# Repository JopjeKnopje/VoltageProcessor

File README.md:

# VoltageProcessor

A eurorack module that outputs the **sum** and **difference** of two inputs, you can also add a constant DC offset to the summing output.

## Motivation
The Beatstep Pro's pitch output cannot go lower than **2V**, the VCO I'm using has a range of approximately **0-5V**, so I had a way to subtract the **2V** off of the pitch output. This module does just that, I intend to just use 1 CV input and a constant DC offset at **-2V** to achieve an output of **0V** with a **2V** input. <br>
You could also use it as a small 2 -> 1 mixer.

### Notes
This is my second KiCad project in a long time so the routing is not the best :) <br>
Measured the current consumption at **1mA @ +12V** and **7mA @ -12V**

## Bill of materials
|Reference|Value                        |Qty   |
|---------|-----------------------------|------|
|C1,C2,C3,C4|0.1uF                        |4     |
|C5,C6    |47uF                         |2     |
|J1,J2,J4,J5|PJ301M-12                    |4     |
|J3       |Eurorack power               |1     |
|R1,R2,R3,R4,R5,R6,R7,R8,R9,R10,R11,R12|100k                         |12    |
|R13,R14  |1k                           |2     |
|R15,R16  |10k                          |2     |
|RV1,RV2,RV3|100k                         |3     |
|U1       |TL074                        |1     |

[Interactive BOM](https://www.joppeboeve.nl/projects/voltage-processor/ibom.html)

[Falstad simulation](https://tinyurl.com/26u5qrzk)

## Schematic

## KiCad renders

### rev 0.2 -> 0.3 patches
- DC Offset potmeter range is now `+-10` instead of the rail-rail voltage.

### rev 0.1 -> 0.2 patches
- Flip eurorack power connector around y-axis, I currently use a flipped power cable as a workaround.
- Switch `U1B` and `U1B` terminals by adding jumper wire and cutting trace.
- J4 and J5 output should be on pin 3 instead of pin 2. fix by adding jumper wire.

## Todo
- [x] All of the `rev 0.1 patches`
- [ ] Fix jack hole should be 6mm instead of 5.3mm.
- [x] DC Offset potmeter compensate for opamp rail-rail offset which is around 1.3v
- [x] Add polarity symbol in C5 and C6.
- [x] Switch RV1 and RV2 twisting direction.
- [ ] Think about more ergonomic potmeter position.
- [x] Front panel
- [x] Produce and test rev 0.1

## Resources
[Summing Amplifier](https://www.electronics-tutorials.ws/opamp/opamp_4.html) 

[Differential Amplifier](https://www.electronics-tutorials.ws/opamp/opamp_5.html)

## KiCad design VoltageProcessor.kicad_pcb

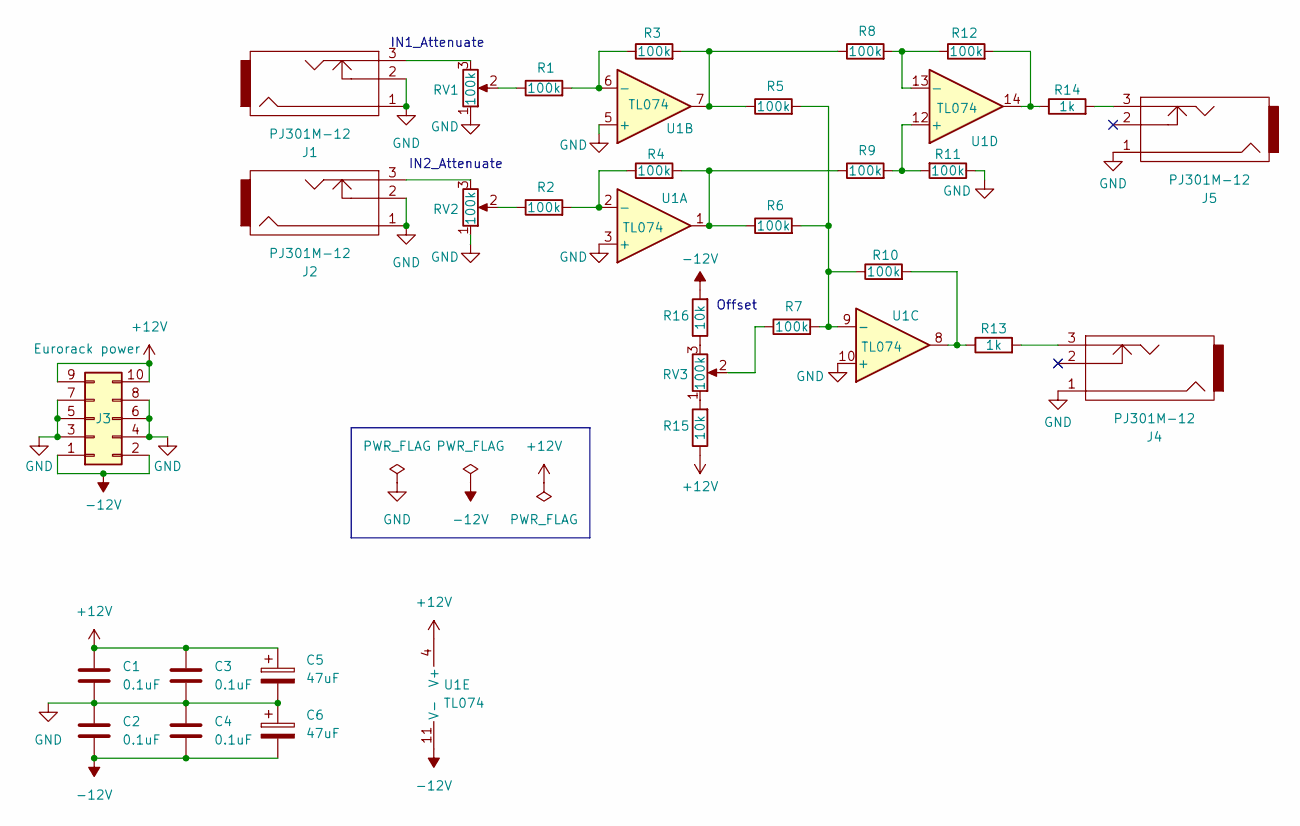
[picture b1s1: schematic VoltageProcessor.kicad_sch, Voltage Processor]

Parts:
C1, C2, C3, C4: 0.1uF; C_Disc_D5.0mm_W2.5mm_P2.50mm
C5, C6: 47uF; CP_Radial_D5.0mm_P2.00mm
J1, J2, J4, J5: PJ301M-12
J3: Eurorack power; IDC-Header_2x05_P2.54mm_Vertical
R1, R2, R3, R4, R5, R6, R7, R8, R9, R10, R11, R12: 100k; R_Axial_DIN0204_L3.6mm_D1.6mm_P7.62mm_Horizontal
R13, R14: 1k; R_Axial_DIN0204_L3.6mm_D1.6mm_P7.62mm_Horizontal
R15, R16: 10k; R_Axial_DIN0204_L3.6mm_D1.6mm_P7.62mm_Horizontal
RV1, RV2, RV3: 100k; trimmer_alps-rk09k1130ah1
U1: TL074; DIP-14_W7.62mm

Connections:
+12V: C1.1, C3.1, C5.1, J3.9, J3.10, R15.1, U1.4 (V+)
-12V: C2.2, C4.2, C6.2, J3.1, J3.2, R16.2, U1.11 (V-)
GND: C1.2, C2.1, C3.2, C4.1, C5.2, C6.1, J1.1, J1.2, J2.1, J2.2, J3.3, J3.4, J3.5, J3.6, J3.7, J3.8, J4.1, J5.1, R11.1, RV1.1, RV2.1, U1.3 (+), U1.5 (+), U1.10 (+)
unnamed: J1.3, RV1.3
unnamed: J2.3, RV2.3
unnamed: J4.3, R13.2
unnamed: J5.3, R14.2
unnamed: R1.1, RV1.2
unnamed: R2.1, RV2.2
unnamed: R3.2, R5.1, R8.1, U1.7
unnamed: R4.2, R6.1, R9.1, U1.1
unnamed: R7.1, RV3.2
unnamed: R10.2, R13.1, U1.8
unnamed: R12.2, R14.1, U1.14
unnamed: R15.2, RV3.1
unnamed: R16.1, RV3.3
unnamed: R2.2, R4.1, U1.2 (-)
unnamed: R1.2, R3.1, U1.6 (-)
unnamed: R5.2, R6.2, R7.2, R10.1, U1.9 (-)
unnamed: R9.2, R11.2, U1.12 (+)
unnamed: R8.2, R12.1, U1.13 (-)

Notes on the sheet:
IN1_Attenuate
Offset
IN2_Attenuate

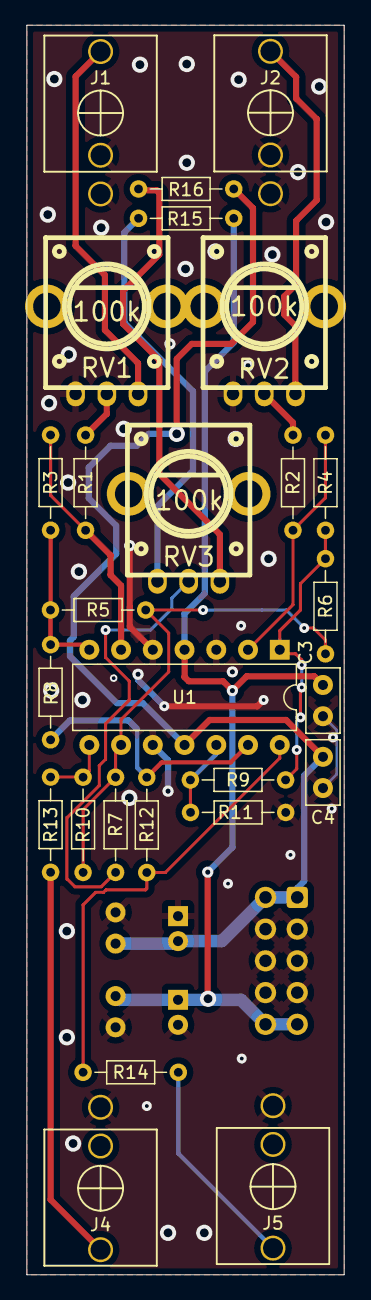
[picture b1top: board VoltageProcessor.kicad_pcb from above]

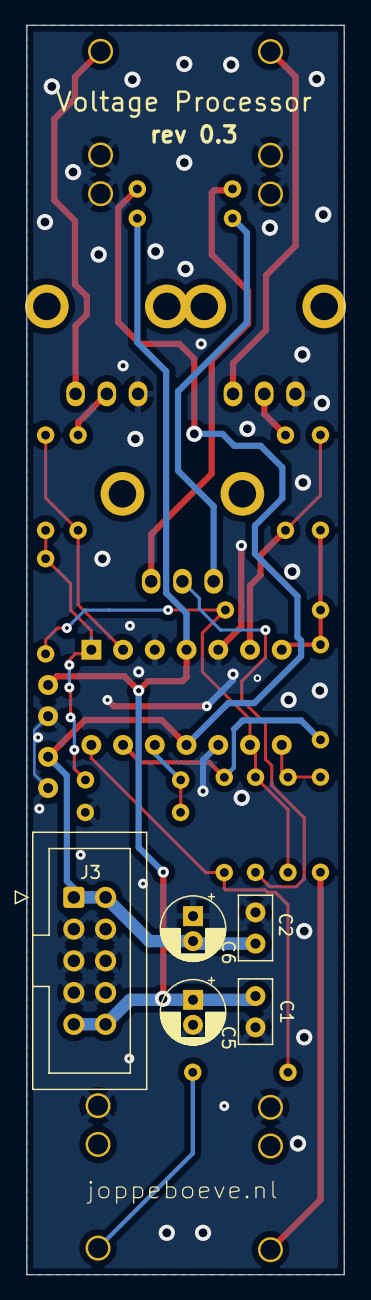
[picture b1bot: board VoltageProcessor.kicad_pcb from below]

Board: 2 copper layers, 25.4 x 100.0 mm, 31 parts (5 on the bottom side), 21 nets.

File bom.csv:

"Reference","Value","Qty"
"C1,C2,C3,C4","0.1uF","4"
"C5,C6","47uF","2"
"J1,J2,J4,J5","PJ301M-12","4"
"J3","Eurorack power","1"
"R1,R2,R3,R4,R5,R6,R7,R8,R9,R10,R11,R12","100k","12"
"R13,R14","1k","2"
"R15,R16","10k","2"
"RV1,RV2,RV3","100k","3"
"U1","TL074","1"

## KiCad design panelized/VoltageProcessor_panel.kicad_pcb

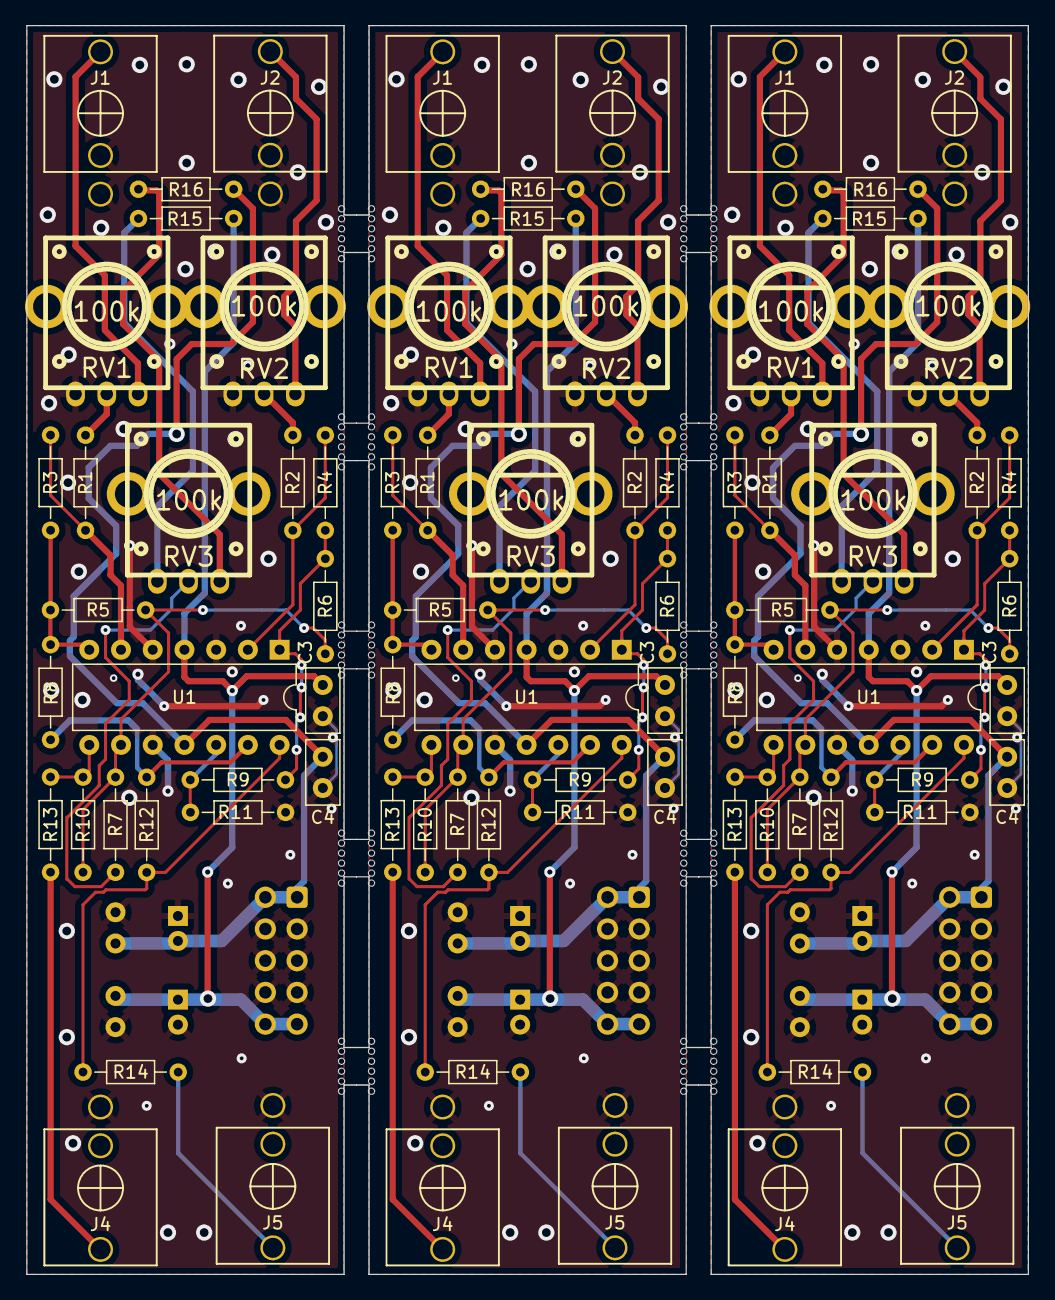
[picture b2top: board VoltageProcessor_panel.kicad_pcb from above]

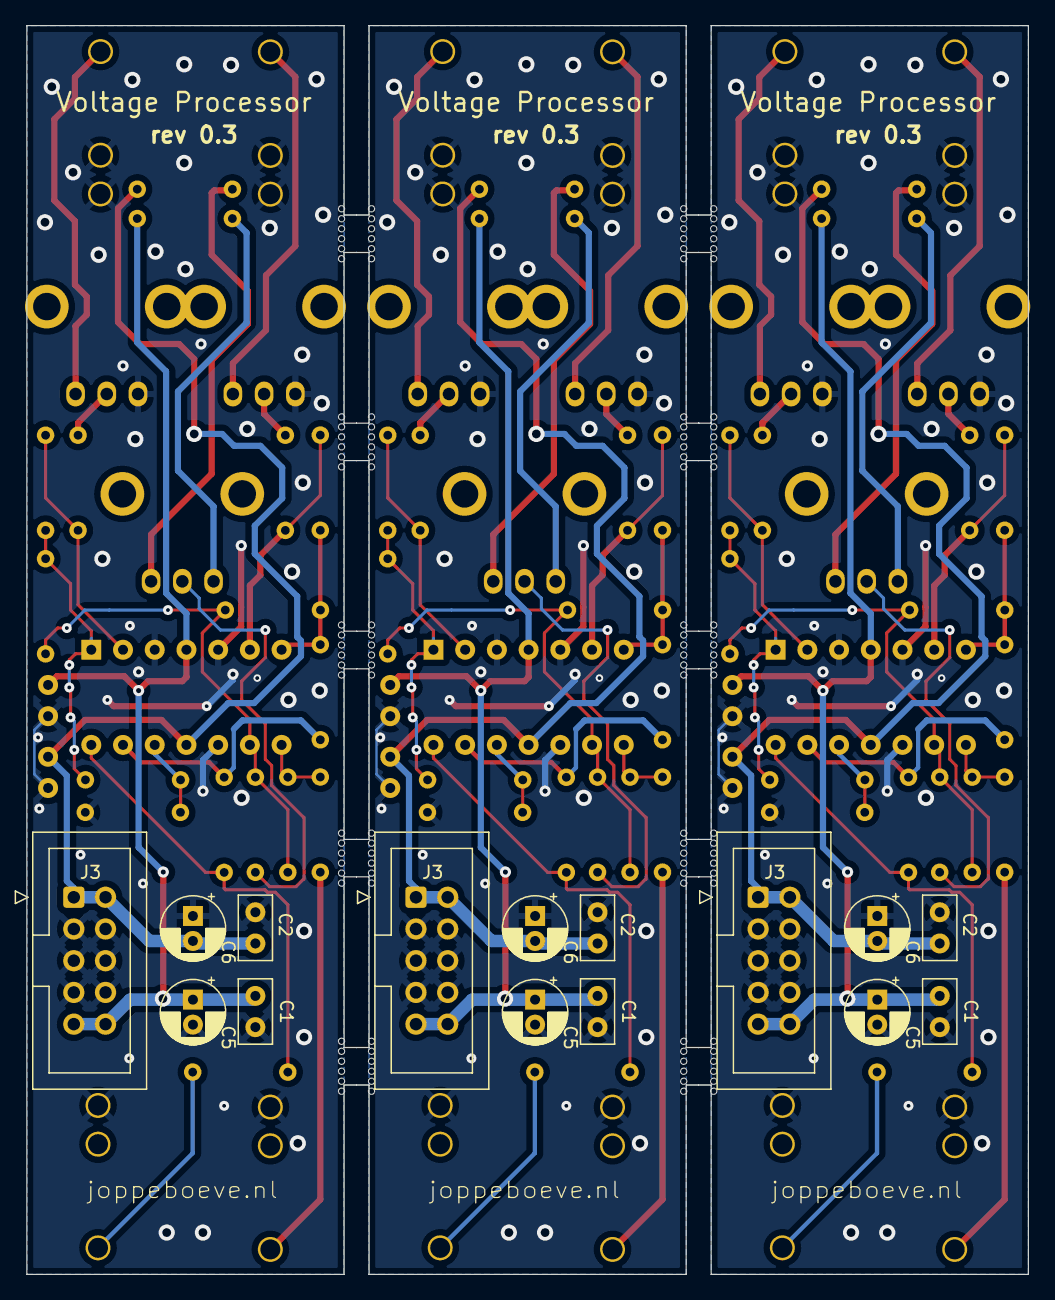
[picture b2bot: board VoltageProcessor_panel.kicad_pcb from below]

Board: 2 copper layers, 80.2 x 100.0 mm, 213 parts (15 on the bottom side), 63 nets.

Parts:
C1, C1#2, C1#3, C2, C2#2, C2#3, C3, C3#2, C3#3, C4, C4#2, C4#3: 0.1uF; C_Disc_D5.0mm_W2.5mm_P2.50mm
C5, C5#2, C5#3, C6, C6#2, C6#3: 47uF; CP_Radial_D5.0mm_P2.00mm
J1, J1#2, J1#3, J2, J2#2, J2#3, J4, J4#2, J4#3, J5, J5#2, J5#3: PJ301M-12
J3, J3#2, J3#3: Eurorack power; IDC-Header_2x05_P2.54mm_Vertical
KiKit_MB_1_1, KiKit_MB_1_2, KiKit_MB_1_3, KiKit_MB_1_4, KiKit_MB_1_5, KiKit_MB_1_6, KiKit_MB_2_1, KiKit_MB_2_2, KiKit_MB_2_3, KiKit_MB_2_4, KiKit_MB_2_5, KiKit_MB_2_6, KiKit_MB_3_1, KiKit_MB_3_2, KiKit_MB_3_3, KiKit_MB_3_4, KiKit_MB_3_5, KiKit_MB_3_6, KiKit_MB_4_1, KiKit_MB_4_2, KiKit_MB_4_3, KiKit_MB_4_4, KiKit_MB_4_5, KiKit_MB_4_6, KiKit_MB_5_1, KiKit_MB_5_2, KiKit_MB_5_3, KiKit_MB_5_4, KiKit_MB_5_5, KiKit_MB_5_6, KiKit_MB_6_1, KiKit_MB_6_2, KiKit_MB_6_3, KiKit_MB_6_4, KiKit_MB_6_5, KiKit_MB_6_6, KiKit_MB_7_1, KiKit_MB_7_2, KiKit_MB_7_3, KiKit_MB_7_4, KiKit_MB_7_5, KiKit_MB_7_6, KiKit_MB_8_1, KiKit_MB_8_2, KiKit_MB_8_3, KiKit_MB_8_4, KiKit_MB_8_5, KiKit_MB_8_6, KiKit_MB_9_1, KiKit_MB_9_2, KiKit_MB_9_3, KiKit_MB_9_4, KiKit_MB_9_5, KiKit_MB_9_6, KiKit_MB_10_1, KiKit_MB_10_2, KiKit_MB_10_3, KiKit_MB_10_4, KiKit_MB_10_5, KiKit_MB_10_6, KiKit_MB_11_1, KiKit_MB_11_2, KiKit_MB_11_3, KiKit_MB_11_4, KiKit_MB_11_5, KiKit_MB_11_6, KiKit_MB_12_1, KiKit_MB_12_2, KiKit_MB_12_3, KiKit_MB_12_4, KiKit_MB_12_5, KiKit_MB_12_6, KiKit_MB_13_1, KiKit_MB_13_2, KiKit_MB_13_3, KiKit_MB_13_4, KiKit_MB_13_5, KiKit_MB_13_6, KiKit_MB_14_1, KiKit_MB_14_2, KiKit_MB_14_3, KiKit_MB_14_4, KiKit_MB_14_5, KiKit_MB_14_6, KiKit_MB_15_1, KiKit_MB_15_2, KiKit_MB_15_3, KiKit_MB_15_4, KiKit_MB_15_5, KiKit_MB_15_6, KiKit_MB_16_1, KiKit_MB_16_2, KiKit_MB_16_3, KiKit_MB_16_4, KiKit_MB_16_5, KiKit_MB_16_6, KiKit_MB_17_1, KiKit_MB_17_2, KiKit_MB_17_3, KiKit_MB_17_4, KiKit_MB_17_5, KiKit_MB_17_6, KiKit_MB_18_1, KiKit_MB_18_2, KiKit_MB_18_3, KiKit_MB_18_4, KiKit_MB_18_5, KiKit_MB_18_6, KiKit_MB_19_1, KiKit_MB_19_2, KiKit_MB_19_3, KiKit_MB_19_4, KiKit_MB_19_5, KiKit_MB_19_6, KiKit_MB_20_1, KiKit_MB_20_2, KiKit_MB_20_3, KiKit_MB_20_4, KiKit_MB_20_5, KiKit_MB_20_6: NPTH
R1, R1#2, R1#3, R2, R2#2, R2#3, R3, R3#2, R3#3, R4, R4#2, R4#3, R5, R5#2, R5#3, R6, R6#2, R6#3, R7, R7#2, R7#3, R8, R8#2, R8#3, R9, R9#2, R9#3, R10, R10#2, R10#3, R11, R11#2, R11#3, R12, R12#2, R12#3: 100k; R_Axial_DIN0204_L3.6mm_D1.6mm_P7.62mm_Horizontal
R13, R13#2, R13#3, R14, R14#2, R14#3: 1k; R_Axial_DIN0204_L3.6mm_D1.6mm_P7.62mm_Horizontal
R15, R15#2, R15#3, R16, R16#2, R16#3: 10k; R_Axial_DIN0204_L3.6mm_D1.6mm_P7.62mm_Horizontal
RV1, RV1#2, RV1#3, RV2, RV2#2, RV2#3, RV3, RV3#2, RV3#3: 100k; trimmer_alps-rk09k1130ah1
U1, U1#2, U1#3: TL074; DIP-14_W7.62mm

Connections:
Board_0-+12V: C1#2.1, C3#2.1, C5.1, J3#3.9, J3#3.10, R15#2.1, U1#2.4 (V+)
Board_0--12V: C2#3.2, C4#2.2, C6#2.2, J3#3.1, J3#3.2, R16#2.2, U1#2.11 (V-)
Board_0-GND: C1#2.2, C2#3.1, C3#2.2, C4#2.1, C5.2, C6#2.1, J1#2.1, J1#2.2, J2.1, J2.2, J3#3.3, J3#3.4, J3#3.5, J3#3.6, J3#3.7, J3#3.8, J4#3.1, J5#2.1, R11#2.1, RV1.1, RV2#2.1, U1#2.3 (+), U1#2.5 (+), U1#2.10 (+)
Board_0-Net-(J1-Pad3): J1#2.3, RV1.3
Board_0-Net-(J2-Pad3): J2.3, RV2#2.3
Board_0-Net-(J4-Pad3): J4#3.3, R13#2.2
Board_0-Net-(J5-Pad3): J5#2.3, R14#2.2
Board_0-Net-(R1-Pad1): R1.1, RV1.2
Board_0-Net-(R2-Pad1): R2#2.1, RV2#2.2
Board_0-Net-(R3-Pad2): R3#3.2, R5#2.1, R8#2.1, U1#2.7
Board_0-Net-(R4-Pad2): R4#2.2, R6#3.1, R9.1, U1#2.1
Board_0-Net-(R7-Pad1): R7#3.1, RV3.2
Board_0-Net-(R10-Pad2): R10#3.2, R13#2.1, U1#2.8
Board_0-Net-(R12-Pad2): R12.2, R14#2.1, U1#2.14
Board_0-Net-(R15-Pad2): R15#2.2, RV3.1
Board_0-Net-(R16-Pad1): R16#2.1, RV3.3
Board_0-Net-(U1A--): R2#2.2, R4#2.1, U1#2.2 (-)
Board_0-Net-(U1B--): R1.2, R3#3.1, U1#2.6 (-)
Board_0-Net-(U1C--): R5#2.2, R6#3.2, R7#3.2, R10#3.1, U1#2.9 (-)
Board_0-Net-(U1D-+): R9.2, R11#2.2, U1#2.12 (+)
Board_0-Net-(U1D--): R8#2.2, R12.1, U1#2.13 (-)
Board_1-+12V: C1.1, C3.1, C5#2.1, J3.9, J3.10, R15.1, U1.4 (V+)
Board_1--12V: C2#2.2, C4.2, C6.2, J3.1, J3.2, R16#3.2, U1.11 (V-)
Board_1-GND: C1.2, C2#2.1, C3.2, C4.1, C5#2.2, C6.1, J1#3.1, J1#3.2, J2#3.1, J2#3.2, J3.3, J3.4, J3.5, J3.6, J3.7, J3.8, J4.1, J5#3.1, R11.1, RV1#3.1, RV2#3.1, U1.3 (+), U1.5 (+), U1.10 (+)
Board_1-Net-(J1-Pad3): J1#3.3, RV1#3.3
Board_1-Net-(J2-Pad3): J2#3.3, RV2#3.3
Board_1-Net-(J4-Pad3): J4.3, R13#3.2
Board_1-Net-(J5-Pad3): J5#3.3, R14.2
Board_1-Net-(R1-Pad1): R1#3.1, RV1#3.2
Board_1-Net-(R2-Pad1): R2#3.1, RV2#3.2
Board_1-Net-(R3-Pad2): R3#2.2, R5.1, R8.1, U1.7
Board_1-Net-(R4-Pad2): R4#3.2, R6#2.1, R9#2.1, U1.1
Board_1-Net-(R7-Pad1): R7#2.1, RV3#3.2
Board_1-Net-(R10-Pad2): R10.2, R13#3.1, U1.8
Board_1-Net-(R12-Pad2): R12#3.2, R14.1, U1.14
Board_1-Net-(R15-Pad2): R15.2, RV3#3.1
Board_1-Net-(R16-Pad1): R16#3.1, RV3#3.3
Board_1-Net-(U1A--): R2#3.2, R4#3.1, U1.2 (-)
Board_1-Net-(U1B--): R1#3.2, R3#2.1, U1.6 (-)
Board_1-Net-(U1C--): R5.2, R6#2.2, R7#2.2, R10.1, U1.9 (-)
Board_1-Net-(U1D-+): R9#2.2, R11.2, U1.12 (+)
Board_1-Net-(U1D--): R8.2, R12#3.1, U1.13 (-)
Board_2-+12V: C1#3.1, C3#3.1, C5#3.1, J3#2.9, J3#2.10, R15#3.1, U1#3.4 (V+)
Board_2--12V: C2.2, C4#3.2, C6#3.2, J3#2.1, J3#2.2, R16.2, U1#3.11 (V-)
Board_2-GND: C1#3.2, C2.1, C3#3.2, C4#3.1, C5#3.2, C6#3.1, J1.1, J1.2, J2#2.1, J2#2.2, J3#2.3, J3#2.4, J3#2.5, J3#2.6, J3#2.7, J3#2.8, J4#2.1, J5.1, R11#3.1, RV1#2.1, RV2.1, U1#3.3 (+), U1#3.5 (+), U1#3.10 (+)
Board_2-Net-(J1-Pad3): J1.3, RV1#2.3
Board_2-Net-(J2-Pad3): J2#2.3, RV2.3
Board_2-Net-(J4-Pad3): J4#2.3, R13.2
Board_2-Net-(J5-Pad3): J5.3, R14#3.2
Board_2-Net-(R1-Pad1): R1#2.1, RV1#2.2
Board_2-Net-(R2-Pad1): R2.1, RV2.2
Board_2-Net-(R3-Pad2): R3.2, R5#3.1, R8#3.1, U1#3.7
Board_2-Net-(R4-Pad2): R4.2, R6.1, R9#3.1, U1#3.1
Board_2-Net-(R7-Pad1): R7.1, RV3#2.2
Board_2-Net-(R10-Pad2): R10#2.2, R13.1, U1#3.8
Board_2-Net-(R12-Pad2): R12#2.2, R14#3.1, U1#3.14
Board_2-Net-(R15-Pad2): R15#3.2, RV3#2.1
Board_2-Net-(R16-Pad1): R16.1, RV3#2.3
Board_2-Net-(U1A--): R2.2, R4.1, U1#3.2 (-)
Board_2-Net-(U1B--): R1#2.2, R3.1, U1#3.6 (-)
Board_2-Net-(U1C--): R5#3.2, R6.2, R7.2, R10#2.1, U1#3.9 (-)
Board_2-Net-(U1D-+): R9#3.2, R11#3.2, U1#3.12 (+)
Board_2-Net-(U1D--): R8#3.2, R12#2.1, U1#3.13 (-)

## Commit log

2024-07-26 IO Placement
2024-07-26 Pre route
2024-07-26 Done with routing but DRC issues
2024-07-26 Fix most DRC errors
2024-07-28 Add silkscreen text, and last DRC issues
2024-07-28 Add 3D models
2024-07-28 Add image to readme
2024-07-28 Connected input CV jack's switch to GND instead of NC Add schematic picture
2024-07-28 remove `)` from README.md
2024-07-28 Add gerbers Add 3D model back in Add kikit makefile to generate panel
2024-07-28 Add panelized files
2024-07-28 Add FrontPanel
2024-07-28 Add frontpanel gerbers
2024-07-28 Change Makefile Add FrontPanel_panels
2024-07-28 Actually add front_panel gebers
2024-08-02 Found some bugs while assembling the board
2024-08-02 Add issues
2024-08-05 Swapped `U1B` inputs to match that of `U1A`, so that it does work
2024-08-05 Switched `RV1` and `RV2`
2024-08-05 Implemented fixes in schematic
2024-08-05 Remove all tracks
2024-08-05 New routing implenting the fixes for rev 0.1
2024-08-05 Went with old routing instead, with the fixes implemented in the PCB layout. Update README.md
2024-08-12 Add todo
2024-10-09 Add `R15` `R16` to DC Offset potmeter its range is now `+-10` instead of the `rail-rail` voltage. Add small changes in routing to accomodate the resistors. Add change text to `rev 0.3`
2024-10-09 Change schematic page to `rev 0.3`
2024-10-18 Change schematic page to `rev 0.3` Add BOM Change README
2024-10-19 Change schematic page to `rev 0.3` Add BOM and interactive BOM Change README
